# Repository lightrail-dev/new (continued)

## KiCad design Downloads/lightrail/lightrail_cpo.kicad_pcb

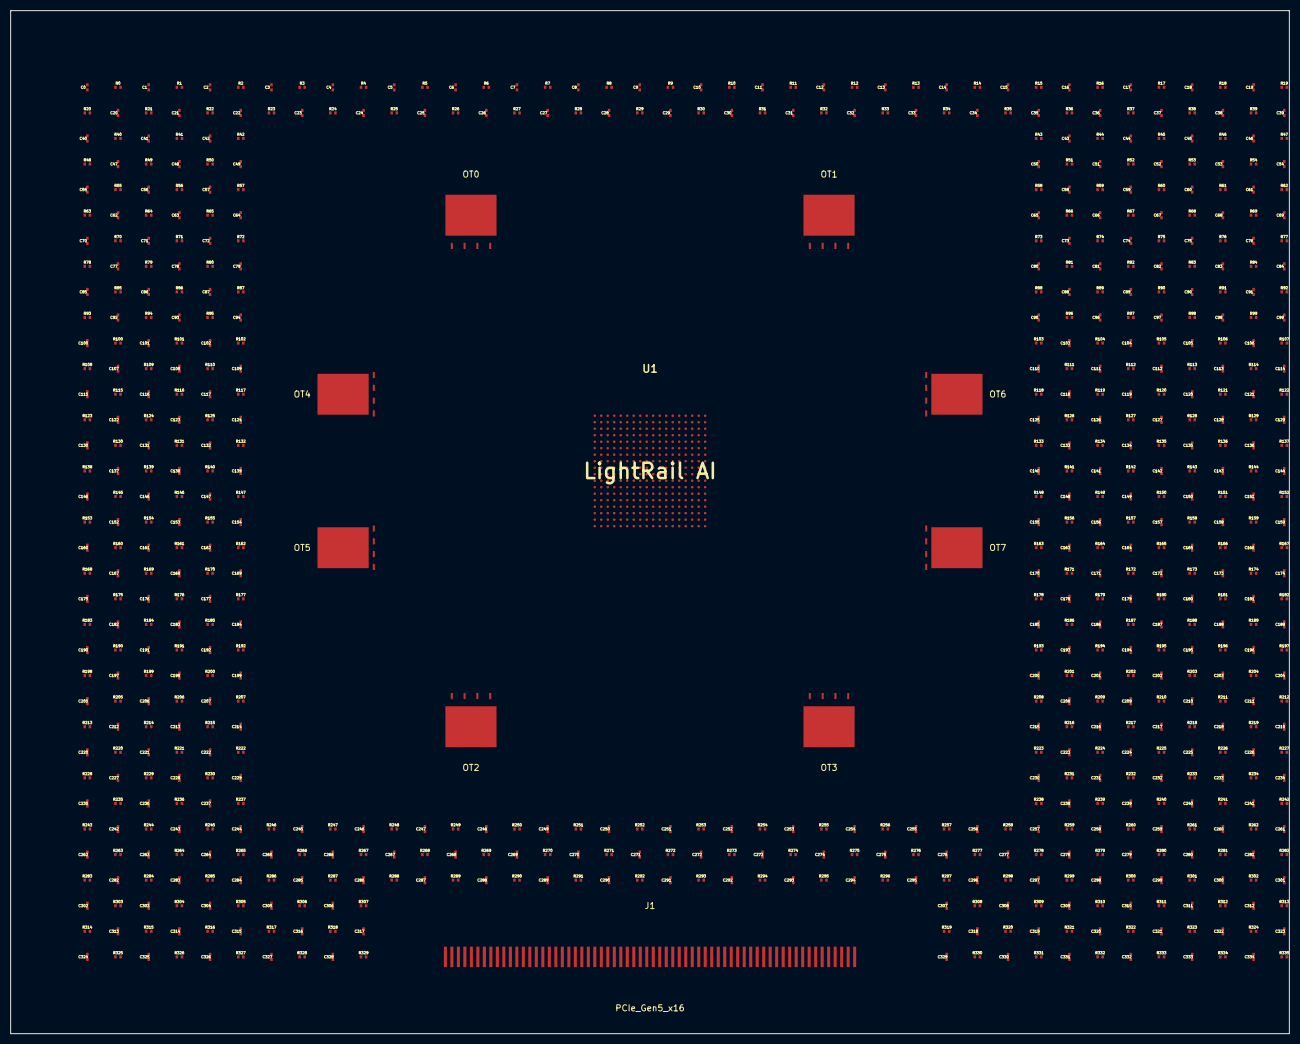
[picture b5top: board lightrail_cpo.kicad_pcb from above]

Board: 15 copper layers, 250.0 x 200.0 mm, 681 parts (0 on the bottom side), 77 nets, no tracks yet.

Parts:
C0, C1, C2, C3, C4, C5, C6, C7, C8, C9, C10, C11, C12, C13, C14, C15, C16, C17, C18, C19, C20, C21, C22, C23, C24, C25, C26, C27, C28, C29, C30, C31, C32, C33, C34, C35, C36, C37, C38, C39, C40, C41, C42, C43, C44, C45, C46, C47, C48, C49, C50, C51, C52, C53, C54, C55, C56, C57, C58, C59, C60, C61, C62, C63, C64, C65, C66, C67, C68, C69, C70, C71, C72, C73, C74, C75, C76, C77, C78, C79, C80, C81, C82, C83, C84, C85, C86, C87, C88, C89, C90, C91, C92, C93, C94, C95, C96, C97, C98, C99, C100, C101, C102, C103, C104, C105, C106, C107, C108, C109, C110, C111, C112, C113, C114, C115, C116, C117, C118, C119, C120, C121, C122, C123, C124, C125, C126, C127, C128, C129, C130, C131, C132, C133, C134, C135, C136, C137, C138, C139, C140, C141, C142, C143, C144, C145, C146, C147, C148, C149, C150, C151, C152, C153, C154, C155, C156, C157, C158, C159, C160, C161, C162, C163, C164, C165, C166, C167, C168, C169, C170, C171, C172, C173, C174, C175, C176, C177, C178, C179, C180, C181, C182, C183, C184, C185, C186, C187, C188, C189, C190, C191, C192, C193, C194, C195, C196, C197, C198, C199, C200, C201, C202, C203, C204, C205, C206, C207, C208, C209, C210, C211, C212, C213, C214, C215, C216, C217, C218, C219, C220, C221, C222, C223, C224, C225, C226, C227, C228, C229, C230, C231, C232, C233, C234, C235, C236, C237, C238, C239, C240, C241, C242, C243, C244, C245, C246, C247, C248, C249, C250, C251, C252, C253, C254, C255, C256, C257, C258, C259, C260, C261, C262, C263, C264, C265, C266, C267, C268, C269, C270, C271, C272, C273, C274, C275, C276, C277, C278, C279, C280, C281, C282, C283, C284, C285, C286, C287, C288, C289, C290, C291, C292, C293, C294, C295, C296, C297, C298, C299, C300, C301, C302, C303, C304, C305, C306, C307, C308, C309, C310, C311, C312, C313, C314, C315, C316, C317, C318, C319, C320, C321, C322, C323, C324, C325, C326, C327, C328, C329, C330, C331, C332, C333, C334: C; C_0402_1005Metric
J1: PCIe_Gen5_x16; PCIe_x16
OT0, OT1, OT2, OT3, OT4, OT5, OT6, OT7: O_TILE_TFLN
R0, R1, R2, R3, R4, R5, R6, R7, R8, R9, R10, R11, R12, R13, R14, R15, R16, R17, R18, R19, R20, R21, R22, R23, R24, R25, R26, R27, R28, R29, R30, R31, R32, R33, R34, R35, R36, R37, R38, R39, R40, R41, R42, R43, R44, R45, R46, R47, R48, R49, R50, R51, R52, R53, R54, R55, R56, R57, R58, R59, R60, R61, R62, R63, R64, R65, R66, R67, R68, R69, R70, R71, R72, R73, R74, R75, R76, R77, R78, R79, R80, R81, R82, R83, R84, R85, R86, R87, R88, R89, R90, R91, R92, R93, R94, R95, R96, R97, R98, R99, R100, R101, R102, R103, R104, R105, R106, R107, R108, R109, R110, R111, R112, R113, R114, R115, R116, R117, R118, R119, R120, R121, R122, R123, R124, R125, R126, R127, R128, R129, R130, R131, R132, R133, R134, R135, R136, R137, R138, R139, R140, R141, R142, R143, R144, R145, R146, R147, R148, R149, R150, R151, R152, R153, R154, R155, R156, R157, R158, R159, R160, R161, R162, R163, R164, R165, R166, R167, R168, R169, R170, R171, R172, R173, R174, R175, R176, R177, R178, R179, R180, R181, R182, R183, R184, R185, R186, R187, R188, R189, R190, R191, R192, R193, R194, R195, R196, R197, R198, R199, R200, R201, R202, R203, R204, R205, R206, R207, R208, R209, R210, R211, R212, R213, R214, R215, R216, R217, R218, R219, R220, R221, R222, R223, R224, R225, R226, R227, R228, R229, R230, R231, R232, R233, R234, R235, R236, R237, R238, R239, R240, R241, R242, R243, R244, R245, R246, R247, R248, R249, R250, R251, R252, R253, R254, R255, R256, R257, R258, R259, R260, R261, R262, R263, R264, R265, R266, R267, R268, R269, R270, R271, R272, R273, R274, R275, R276, R277, R278, R279, R280, R281, R282, R283, R284, R285, R286, R287, R288, R289, R290, R291, R292, R293, R294, R295, R296, R297, R298, R299, R300, R301, R302, R303, R304, R305, R306, R307, R308, R309, R310, R311, R312, R313, R314, R315, R316, R317, R318, R319, R320, R321, R322, R323, R324, R325, R326, R327, R328, R329, R330, R331, R332, R333, R334, R335: R; R_0402_1005Metric
U1: LightRail AI; BGA-324

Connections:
GND: C0.2, C1.2, C2.2, C3.2, C4.2, C5.2, C6.2, C7.2, C8.2, C9.2, C10.2, C11.2, C12.2, C13.2, C14.2, C15.2, C16.2, C17.2, C18.2, C19.2, C20.2, C21.2, C22.2, C23.2, C24.2, C25.2, C26.2, C27.2, C28.2, C29.2, C30.2, C31.2, C32.2, C33.2, C34.2, C35.2, C36.2, C37.2, C38.2, C39.2, C40.2, C41.2, C42.2, C43.2, C44.2, C45.2, C46.2, C47.2, C48.2, C49.2, C50.2, C51.2, C52.2, C53.2, C54.2, C55.2, C56.2, C57.2, C58.2, C59.2, C60.2, C61.2, C62.2, C63.2, C64.2, C65.2, C66.2, C67.2, C68.2, C69.2, C70.2, C71.2, C72.2, C73.2, C74.2, C75.2, C76.2, C77.2, C78.2, C79.2, C80.2, C81.2, C82.2, C83.2, C84.2, C85.2, C86.2, C87.2, C88.2, C89.2, C90.2, C91.2, C92.2, C93.2, C94.2, C95.2, C96.2, C97.2, C98.2, C99.2, C100.2, C101.2, C102.2, C103.2, C104.2, C105.2, C106.2, C107.2, C108.2, C109.2, C110.2, C111.2, C112.2, C113.2, C114.2, C115.2, C116.2, C117.2, C118.2, C119.2, C120.2, C121.2, C122.2, C123.2, C124.2, C125.2, C126.2, C127.2, C128.2, C129.2, C130.2, C131.2, C132.2, C133.2, C134.2, C135.2, C136.2, C137.2, C138.2, C139.2, C140.2, C141.2, C142.2, C143.2, C144.2, C145.2, C146.2, C147.2, C148.2, C149.2, C150.2, C151.2, C152.2, C153.2, C154.2, C155.2, C156.2, C157.2, C158.2, C159.2, C160.2, C161.2, C162.2, C163.2, C164.2, C165.2, C166.2, C167.2, C168.2, C169.2, C170.2, C171.2, C172.2, C173.2, C174.2, C175.2, C176.2, C177.2, C178.2, C179.2, C180.2, C181.2, C182.2, C183.2, C184.2, C185.2, C186.2, C187.2, C188.2, C189.2, C190.2, C191.2, C192.2, C193.2, C194.2, C195.2, C196.2, C197.2, C198.2, C199.2, C200.2, C201.2, C202.2, C203.2, C204.2, C205.2, C206.2, C207.2, C208.2, C209.2, C210.2, C211.2, C212.2, C213.2, C214.2, C215.2, C216.2, C217.2, C218.2, C219.2, C220.2, C221.2, C222.2, C223.2, C224.2, C225.2, C226.2, C227.2, C228.2, C229.2, C230.2, C231.2, C232.2, C233.2, C234.2, C235.2, C236.2, C237.2, C238.2, C239.2, C240.2, C241.2, C242.2, C243.2, C244.2, C245.2, C246.2, C247.2, C248.2, C249.2, C250.2, C251.2, C252.2, C253.2, C254.2, C255.2, C256.2, C257.2, C258.2, C259.2, C260.2, C261.2, C262.2, C263.2, C264.2, C265.2, C266.2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
NCE_PCIE_L0: J1.1, R32.1, R94.1, R116.1, R149.1, R159.1, R165.1, R284.1, R327.1, U1.1
NCE_PCIE_L1: J1.2, R150.1, R328.1, U1.2
NCE_PCIE_L2: J1.3, R53.1, R83.1, R244.1, R321.1, R331.1, U1.3
NCE_PCIE_L3: J1.4, R108.1, R223.1, R280.1, R318.1, U1.4
NCE_PCIE_L4: J1.5, R16.1, R48.1, R92.1, R189.1, R206.1, R220.1, R251.1, U1.5
NCE_PCIE_L5: J1.6, R28.1, R42.1, R81.1, R194.1, R241.1, R273.1, R277.1, U1.6
NCE_PCIE_L6: J1.7, R78.1, R120.1, R221.1, R297.1, U1.7
NCE_PCIE_L7: J1.8, R69.1, R98.1, U1.8
NCE_PCIE_L8: J1.9, R31.1, R109.1, R147.1, R156.1, R205.1, R239.1, R258.1, U1.9
NCE_PCIE_L9: J1.10, R65.1, R124.1, R197.1, R230.1, R247.1, R255.1, R314.1, U1.10
NCE_PCIE_L10: J1.11, R142.1, R183.1, R228.1, R299.1, U1.11
NCE_PCIE_L11: J1.12, R52.1, R85.1, R96.1, R101.1, R117.1, R174.1, R237.1, U1.12
NCE_PCIE_L12: J1.13, R55.1, R84.1, R113.1, R132.1, R195.1, R213.1, R270.1, U1.13
NCE_PCIE_L13: J1.14, R23.1, R264.1, R271.1, R326.1, U1.14
NCE_PCIE_L14: J1.15, R11.1, R45.1, R166.1, U1.15
NCE_PCIE_L15: J1.16, R119.1, R163.1, R164.1, R182.1, R216.1, R289.1, U1.16
NCE_PCIE_L16: J1.17, R198.1, R298.1, R307.1, U1.17
NCE_PCIE_L17: J1.18, R24.1, R47.1, R125.1, R131.1, R246.1, R288.1, R311.1, U1.18
NCE_PCIE_L18: J1.19, R38.1, R115.1, R153.1, R199.1, R224.1, R235.1, U1.19
NCE_PCIE_L19: J1.20, R29.1, R87.1, R152.1, R168.1, R175.1, R181.1, U1.20
NCE_PCIE_L20: J1.21, R12.1, R41.1, R208.1, R262.1, R306.1, U1.21
NCE_PCIE_L21: J1.22, R79.1, R104.1, R137.1, R173.1, R211.1, R249.1, R286.1, U1.22
NCE_PCIE_L22: J1.23, R103.1, R138.1, R186.1, R207.1, R212.1, R253.1, R278.1, U1.23
NCE_PCIE_L23: J1.24, R2.1, R54.1, R95.1, R154.1, R179.1, R188.1, R272.1, R290.1, U1.24
NCE_PCIE_L24: J1.25, R171.1, U1.25
NCE_PCIE_L25: J1.26, R35.1, R56.1, R106.1, R193.1, R243.1, R317.1, R330.1, U1.26
NCE_PCIE_L26: J1.27, R61.1, R90.1, R148.1, R232.1, R238.1, R242.1, U1.27
NCE_PCIE_L27: J1.28, R15.1, R62.1, R89.1, R203.1, R281.1, R287.1, R324.1, U1.28
NCE_PCIE_L28: J1.29, R70.1, R74.1, R86.1, R126.1, R222.1, R254.1, R296.1, U1.29
NCE_PCIE_L29: J1.30, R139.1, R279.1, R294.1, R325.1, U1.30
NCE_PCIE_L30: J1.31, R14.1, R17.1, R93.1, R140.1, R191.1, R196.1, R257.1, U1.31
NCE_PCIE_L31: J1.32, R34.1, R129.1, R141.1, R167.1, R214.1, U1.32
NCE_PCIE_L32: J1.33, R63.1, R172.1, R233.1, U1.33
NCE_PCIE_L33: J1.34, R1.1, R43.1, R44.1, R49.1, R112.1, U1.34
NCE_PCIE_L34: J1.35, R110.1, R170.1, R252.1, U1.35
NCE_PCIE_L35: J1.36, R6.1, R107.1, R133.1, U1.36
NCE_PCIE_L36: J1.37, R46.1, R136.1, R231.1, R315.1, R335.1, U1.37
NCE_PCIE_L37: J1.38, R121.1, R135.1, R145.1, R176.1, R204.1, R210.1, R329.1, U1.38
NCE_PCIE_L38: J1.39, R68.1, R82.1, R97.1, R250.1, U1.39
NCE_PCIE_L39: J1.40, R57.1, R77.1, R122.1, R295.1, U1.40
NCE_PCIE_L40: J1.41, R245.1, R268.1, R322.1, U1.41
NCE_PCIE_L41: J1.42, R8.1, R36.1, R37.1, U1.42
NCE_PCIE_L42: J1.43, R218.1, R227.1, R283.1, R309.1, U1.43
NCE_PCIE_L43: J1.44, R234.1, R261.1, R285.1, R300.1, R301.1, R332.1, U1.44
NCE_PCIE_L44: J1.45, R114.1, R127.1, R209.1, R225.1, R267.1, U1.45
NCE_PCIE_L45: J1.46, R20.1, R157.1, R202.1, R308.1, U1.46
NCE_PCIE_L46: J1.47, R13.1, R27.1, R143.1, R178.1, R303.1, U1.47
NCE_PCIE_L47: J1.48, R22.1, R59.1, R88.1, R130.1, R160.1, R282.1, U1.48
NCE_PCIE_L48: J1.49, R64.1, R72.1, R105.1, R123.1, R269.1, R334.1, U1.49
NCE_PCIE_L49: J1.50, R80.1, R260.1, R316.1, U1.50
NCE_PCIE_L50: J1.51, R73.1, R91.1, R146.1, R155.1, R180.1, U1.51
NCE_PCIE_L51: J1.52, R4.1, R10.1, R58.1, R144.1, R162.1, R226.1, U1.52
NCE_PCIE_L52: J1.53, R51.1, R60.1, R118.1, R274.1, R302.1, U1.53
NCE_PCIE_L53: J1.54, R3.1, R134.1, R192.1, R200.1, R266.1, R320.1, U1.54
NCE_PCIE_L54: J1.55, R67.1, R158.1, R248.1, U1.55
NCE_PCIE_L55: J1.56, R75.1, R76.1, R99.1, R128.1, R263.1, R313.1, R319.1, U1.56
NCE_PCIE_L56: J1.57, R0.1, R26.1, R177.1, R187.1, R215.1, R240.1, R259.1, U1.57
NCE_PCIE_L57: J1.58, R7.1, R21.1, R184.1, R236.1, U1.58
NCE_PCIE_L58: J1.59, R9.1, R40.1, R102.1, R185.1, R201.1, R275.1, R291.1, R310.1, R323.1, U1.59
NCE_PCIE_L59: J1.60, R18.1, R33.1, R71.1, R100.1, R190.1, R217.1, R256.1, U1.60
NCE_PCIE_L60: J1.61, R151.1, R161.1, R219.1, R276.1, R304.1, U1.61
NCE_PCIE_L61: J1.62, R265.1, R305.1, R312.1, U1.62
NCE_PCIE_L62: J1.63, R5.1, R19.1, R25.1, R30.1, R39.1, R66.1, R229.1, U1.63
NCE_PCIE_L63: J1.64, R50.1, R111.1, R169.1, R292.1, R293.1, R333.1, U1.64
O_TILE_0_RF_0: OT0.1, U1.65, U1.73, U1.81, U1.89, U1.97, U1.105, U1.113, U1.121
O_TILE_1_RF_1: OT1.2, U1.66, U1.74, U1.82, U1.90, U1.98, U1.106, U1.114, U1.122
O_TILE_2_RF_2: OT2.3, U1.67, U1.75, U1.83, U1.91, U1.99, U1.107, U1.115, U1.123
O_TILE_3_RF_3: OT3.4, U1.68, U1.76, U1.84, U1.92, U1.100, U1.108, U1.116, U1.124
O_TILE_4_RF_0: OT4.1, U1.69, U1.77, U1.85, U1.93, U1.101, U1.109, U1.117, U1.125
O_TILE_5_RF_1: OT5.2, U1.70, U1.78, U1.86, U1.94, U1.102, U1.110, U1.118, U1.126
O_TILE_6_RF_2: OT6.3, U1.71, U1.79, U1.87, U1.95, U1.103, U1.111, U1.119, U1.127
O_TILE_7_RF_3: OT7.4, U1.72, U1.80, U1.88, U1.96, U1.104, U1.112, U1.120, U1.128
VCC_1V0: U1.134, U1.135, U1.136, U1.137, U1.138, U1.152, U1.153, U1.154, U1.155, U1.156, U1.170, U1.171, U1.172, U1.173, U1.174, U1.188, U1.189, U1.190, U1.191, U1.192, U1.206, U1.207, U1.208, U1.209, U1.210
VCC_1V8: C0.1, C2.1, C3.1, C5.1, C9.1, C17.1, C18.1, C20.1, C24.1, C25.1, C26.1, C28.1, C31.1, C35.1, C37.1, C39.1, C40.1, C43.1, C48.1, C55.1, C60.1, C63.1, C65.1, C70.1, C78.1, C79.1, C87.1, C89.1, C90.1, C91.1, C92.1, C95.1, C107.1, C113.1, C116.1, C118.1, C119.1, C120.1, C122.1, C125.1, C130.1, C133.1, C136.1, C138.1, C139.1, C143.1, C145.1, C146.1, C150.1, C151.1, C155.1, C157.1, C160.1, C166.1, C167.1, C171.1, C174.1, C176.1, C177.1, C178.1, C179.1, C184.1, C185.1, C186.1, C187.1, C189.1, C193.1, C194.1, C195.1, C196.1, C198.1, C200.1, C201.1, C204.1, C207.1, C209.1, C210.1, C211.1, C213.1, C215.1, C217.1, C219.1, C220.1, C227.1, C229.1, C231.1, C233.1, C234.1, C239.1, C241.1, C243.1, C245.1, C253.1, C262.1, C265.1, C267.1, C270.1, C272.1, C274.1, C277.1, C286.1, C288.1, C297.1, C305.1, C306.1, C308.1, C310.1, C311.1, C318.1, C319.1, C322.1, C324.1, C330.1, C332.1
VCC_3V3: C1.1, C10.1, C12.1, C16.1, C19.1, C22.1, C27.1, C30.1, C33.1, C36.1, C38.1, C41.1, C42.1, C44.1, C45.1, C47.1, C51.1, C52.1, C54.1, C56.1, C58.1, C59.1, C62.1, C66.1, C67.1, C69.1, C71.1, C76.1, C80.1, C81.1, C83.1, C86.1, C88.1, C94.1, C96.1, C97.1, C98.1, C99.1, C100.1, C106.1, C111.1, C115.1, C117.1, C123.1, C127.1, C128.1, C132.1, C137.1, C140.1, C144.1, C147.1, C148.1, C158.1, C159.1, C161.1, C162.1, C164.1, C169.1, C172.1, C183.1, C190.1, C202.1, C208.1, C216.1, C218.1, C223.1, C225.1, C228.1, C230.1, C232.1, C235.1, C236.1, C237.1, C238.1, C240.1, C242.1, C244.1, C246.1, C247.1, C249.1, C250.1, C252.1, C257.1, C259.1, C264.1, C268.1, C269.1, C271.1, C275.1, C280.1, C281.1, C282.1, C285.1, C289.1, C293.1, C294.1, C300.1, C302.1, C303.1, C304.1, C307.1, C312.1, C315.1, C316.1, C317.1, C321.1, C327.1, C329.1, C331.1
VCC_12V: C4.1, C6.1, C7.1, C8.1, C11.1, C13.1, C14.1, C15.1, C21.1, C23.1, C29.1, C32.1, C34.1, C46.1, C49.1, C50.1, C53.1, C57.1, C61.1, C64.1, C68.1, C72.1, C73.1, C74.1, C75.1, C77.1, C82.1, C84.1, C85.1, C93.1, C101.1, C102.1, C103.1, C104.1, C105.1, C108.1, C109.1, C110.1, C112.1, C114.1, C121.1, C124.1, C126.1, C129.1, C131.1, C134.1, C135.1, C141.1, C142.1, C149.1, C152.1, C153.1, C154.1, C156.1, C163.1, C165.1, C168.1, C170.1, C173.1, C175.1, C180.1, C181.1, C182.1, C188.1, C191.1, C192.1, C197.1, C199.1, C203.1, C205.1, C206.1, C212.1, C214.1, C221.1, C222.1, C224.1, C226.1, C248.1, C251.1, C254.1, C255.1, C256.1, C258.1, C260.1, C261.1, C263.1, C266.1, C273.1, C276.1, C278.1, C279.1, C283.1, C284.1, C287.1, C290.1, C291.1, C292.1, C295.1, C296.1, C298.1, C299.1, C301.1, C309.1, C313.1, C314.1, C320.1, C323.1, C325.1, C326.1, C328.1, C333.1, C334.1

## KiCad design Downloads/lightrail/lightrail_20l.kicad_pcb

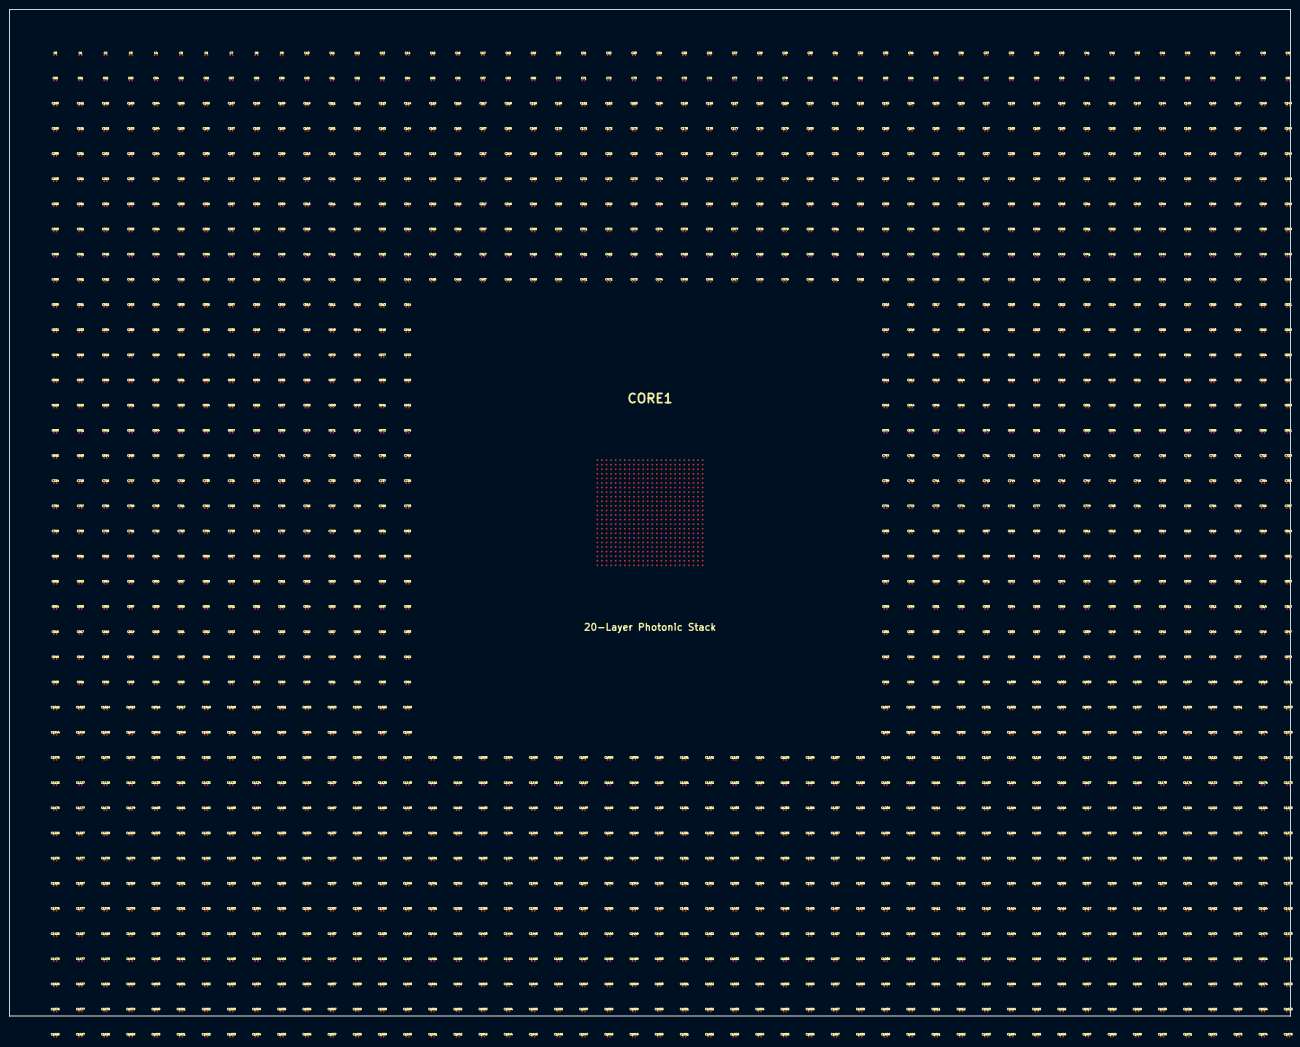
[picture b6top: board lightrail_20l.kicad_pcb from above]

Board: 20 copper layers, 280.0 x 220.0 mm, 1677 parts (0 on the bottom side), 235 nets, no tracks yet.

Parts:
C0, C1, C2, C3, C4, C5, C6, C7, C8, C9, C10, C11, C12, C13, C14, C15, C16, C17, C18, C19, C20, C21, C22, C23, C24, C25, C26, C27, C28, C29, C30, C31, C32, C33, C34, C35, C36, C37, C38, C39, C40, C41, C42, C43, C44, C45, C46, C47, C48, C49, C50, C51, C52, C53, C54, C55, C56, C57, C58, C59, C60, C61, C62, C63, C64, C65, C66, C67, C68, C69, C70, C71, C72, C73, C74, C75, C76, C77, C78, C79, C80, C81, C82, C83, C84, C85, C86, C87, C88, C89, C90, C91, C92, C93, C94, C95, C96, C97, C98, C99, C100, C101, C102, C103, C104, C105, C106, C107, C108, C109, C110, C111, C112, C113, C114, C115, C116, C117, C118, C119, C120, C121, C122, C123, C124, C125, C126, C127, C128, C129, C130, C131, C132, C133, C134, C135, C136, C137, C138, C139, C140, C141, C142, C143, C144, C145, C146, C147, C148, C149, C150, C151, C152, C153, C154, C155, C156, C157, C158, C159, C160, C161, C162, C163, C164, C165, C166, C167, C168, C169, C170, C171, C172, C173, C174, C175, C176, C177, C178, C179, C180, C181, C182, C183, C184, C185, C186, C187, C188, C189, C190, C191, C192, C193, C194, C195, C196, C197, C198, C199, C200, C201, C202, C203, C204, C205, C206, C207, C208, C209, C210, C211, C212, C213, C214, C215, C216, C217, C218, C219, C220, C221, C222, C223, C224, C225, C226, C227, C228, C229, C230, C231, C232, C233, C234, C235, C236, C237, C238, C239, C240, C241, C242, C243, C244, C245, C246, C247, C248, C249, C250, C251, C252, C253, C254, C255, C256, C257, C258, C259, C260, C261, C262, C263, C264, C265, C266, C267, C268, C269, C270, C271, C272, C273, C274, C275, C276, C277, C278, C279, C280, C281, C282, C283, C284, C285, C286, C287, C288, C289, C290, C291, C292, C293, C294, C295, C296, C297, C298, C299, C300, C301, C302, C303, C304, C305, C306, C307, C308, C309, C310, C311, C312, C313, C314, C315, C316, C317, C318, C319, C320, C321, C322, C323, C324, C325, C326, C327, C328, C329, C330, C331, C332, C333, C334, C335, C336, C337, C338, C339, C340, C341, C342, C343, C344, C345, C346, C347, C348, C349, C350, C351, C352, C353, C354, C355, C356, C357, C358, C359, C360, C361, C362, C363, C364, C365, C366, C367, C368, C369, C370, C371, C372, C373, C374, C375, C376, C377, C378, C379, C380, C381, C382, C383, C384, C385, C386, C387, C388, C389, C390, C391, C392, C393, C394, C395, C396, C397, C398, C399, C400, C401, C402, C403, C404, C405, C406, C407, C408, C409, C410, C411, C412, C413, C414, C415, C416, C417, C418, C419, C420, C421, C422, C423, C424, C425, C426, C427, C428, C429, C430, C431, C432, C433, C434, C435, C436, C437, C438, C439, C440, C441, C442, C443, C444, C445, C446, C447, C448, C449, C450, C451, C452, C453, C454, C455, C456, C457, C458, C459, C460, C461, C462, C463, C464, C465, C466, C467, C468, C469, C470, C471, C472, C473, C474, C475, C476, C477, C478, C479, C480, C481, C482, C483, C484, C485, C486, C487, C488, C489, C490, C491, C492, C493, C494, C495, C496, C497, C498, C499, C500, C501, C502, C503, C504, C505, C506, C507, C508, C509, C510, C511, C512, C513, C514, C515, C516, C517, C518, C519, C520, C521, C522, C523, C524, C525, C526, C527, C528, C529, C530, C531, C532, C533, C534, C535, C536, C537, C538, C539, C540, C541, C542, C543, C544, C545, C546, C547, C548, C549, C550, C551, C552, C553, C554, C555, C556, C557, C558, C559, C560, C561, C562, C563, C564, C565, C566, C567, C568, C569, C570, C571, C572, C573, C574, C575, C576, C577, C578, C579, C580, C581, C582, C583, C584, C585, C586, C587, C588, C589, C590, C591, C592, C593, C594, C595, C596, C597, C598, C599, C600, C601, C602, C603, C604, C605, C606, C607, C608, C609, C610, C611, C612, C613, C614, C615, C616, C617, C618, C619, C620, C621, C622, C623, C624, C625, C626, C627, C628, C629, C630, C631, C632, C633, C634, C635, C636, C637, C638, C639, C640, C641, C642, C643, C644, C645, C646, C647, C648, C649, C650, C651, C652, C653, C654, C655, C656, C657, C658, C659, C660, C661, C662, C663, C664, C665, C666, C667, C668, C669, C670, C671, C672, C673, C674, C675, C676, C677, C678, C679, C680, C681, C682, C683, C684, C685, C686, C687, C688, C689, C690, C691, C692, C693, C694, C695, C696, C697, C698, C699, C700, C701, C702, C703, C704, C705, C706, C707, C708, C709, C710, C711, C712, C713, C714, C715, C716, C717, C718, C719, C720, C721, C722, C723, C724, C725, C726, C727, C728, C729, C730, C731, C732, C733, C734, C735, C736, C737, C738, C739, C740, C741, C742, C743, C744, C745, C746, C747, C748, C749, C750, C751, C752, C753, C754, C755, C756, C757, C758, C759, C760, C761, C762, C763, C764, C765, C766, C767, C768, C769, C770, C771, C772, C773, C774, C775, C776, C777, C778, C779, C780, C781, C782, C783, C784, C785, C786, C787, C788, C789, C790, C791, C792, C793, C794, C795, C796, C797, C798, C799, C800, C801, C802, C803, C804, C805, C806, C807, C808, C809, C810, C811, C812, C813, C814, C815, C816, C817, C818, C819, C820, C821, C822, C823, C824, C825, C826, C827, C828, C829, C830, C831, C832, C833, C834, C835, C836, C837, C838, C839, C840, C841, C842, C843, C844, C845, C846, C847, C848, C849, C850, C851, C852, C853, C854, C855, C856, C857, C858, C859, C860, C861, C862, C863, C864, C865, C866, C867, C868, C869, C870, C871, C872, C873, C874, C875, C876, C877, C878, C879, C880, C881, C882, C883, C884, C885, C886, C887, C888, C889, C890, C891, C892, C893, C894, C895, C896, C897, C898, C899, C900, C901, C902, C903, C904, C905, C906, C907, C908, C909, C910, C911, C912, C913, C914, C915, C916, C917, C918, C919, C920, C921, C922, C923, C924, C925, C926, C927, C928, C929, C930, C931, C932, C933, C934, C935, C936, C937, C938, C939, C940, C941, C942, C943, C944, C945, C946, C947, C948, C949, C950, C951, C952, C953, C954, C955, C956, C957, C958, C959, C960, C961, C962, C963, C964, C965, C966, C967, C968, C969, C970, C971, C972, C973, C974, C975, C976, C977, C978, C979, C980, C981, C982, C983, C984, C985, C986, C987, C988, C989, C990, C991, C992, C993, C994, C995, C996, C997, C998, C999, C1000, C1001, C1002, C1003, C1004, C1005, C1006, C1007, C1008, C1009, C1010, C1011, C1012, C1013, C1014, C1015, C1016, C1017, C1018, C1019, C1020, C1021, C1022, C1023, C1024, C1025, C1026, C1027, C1028, C1029, C1030, C1031, C1032, C1033, C1034, C1035, C1036, C1037, C1038, C1039, C1040, C1041, C1042, C1043, C1044, C1045, C1046, C1047, C1048, C1049, C1050, C1051, C1052, C1053, C1054, C1055, C1056, C1057, C1058, C1059, C1060, C1061, C1062, C1063, C1064, C1065, C1066, C1067, C1068, C1069, C1070, C1071, C1072, C1073, C1074, C1075, C1076, C1077, C1078, C1079, C1080, C1081, C1082, C1083, C1084, C1085, C1086, C1087, C1088, C1089, C1090, C1091, C1092, C1093, C1094, C1095, C1096, C1097, C1098, C1099, C1100, C1101, C1102, C1103, C1104, C1105, C1106, C1107, C1108, C1109, C1110, C1111, C1112, C1113, C1114, C1115, C1116, C1117, C1118, C1119, C1120, C1121, C1122, C1123, C1124, C1125, C1126, C1127, C1128, C1129, C1130, C1131, C1132, C1133, C1134, C1135, C1136, C1137, C1138, C1139, C1140, C1141, C1142, C1143, C1144, C1145, C1146, C1147, C1148, C1149, C1150, C1151, C1152, C1153, C1154, C1155, C1156, C1157, C1158, C1159, C1160, C1161, C1162, C1163, C1164, C1165, C1166, C1167, C1168, C1169, C1170, C1171, C1172, C1173, C1174, C1175, C1176, C1177, C1178, C1179, C1180, C1181, C1182, C1183, C1184, C1185, C1186, C1187, C1188, C1189, C1190, C1191, C1192, C1193, C1194, C1195, C1196, C1197, C1198, C1199, C1200, C1201, C1202, C1203, C1204, C1205, C1206, C1207, C1208, C1209, C1210, C1211, C1212, C1213, C1214, C1215, C1216, C1217, C1218, C1219, C1220, C1221, C1222, C1223, C1224, C1225, C1226, C1227, C1228, C1229, C1230, C1231, C1232, C1233, C1234, C1235, C1236, C1237, C1238, C1239, C1240, C1241, C1242, C1243, C1244, C1245, C1246, C1247, C1248, C1249, C1250, C1251, C1252, C1253, C1254, C1255, C1256, C1257, C1258, C1259, C1260, C1261, C1262, C1263, C1264, C1265, C1266, C1267, C1268, C1269, C1270, C1271, C1272, C1273, C1274, C1275, C1276, C1277, C1278, C1279, C1280, C1281, C1282, C1283, C1284, C1285, C1286, C1287, C1288, C1289, C1290, C1291, C1292, C1293, C1294, C1295, C1296, C1297, C1298, C1299, C1300, C1301, C1302, C1303, C1304, C1305, C1306, C1307, C1308, C1309, C1310, C1311, C1312, C1313, C1314, C1315, C1316, C1317, C1318, C1319, C1320, C1321, C1322, C1323, C1324, C1325, C1326, C1327, C1328, C1329, C1330, C1331, C1332, C1333, C1334, C1335, C1336, C1337, C1338, C1339, C1340, C1341, C1342, C1343, C1344, C1345, C1346, C1347, C1348, C1349, C1350, C1351, C1352, C1353, C1354, C1355, C1356, C1357, C1358, C1359, C1360, C1361, C1362, C1363, C1364, C1365, C1366, C1367, C1368, C1369, C1370, C1371, C1372, C1373, C1374, C1375, C1376, C1377, C1378, C1379, C1380, C1381, C1382, C1383, C1384, C1385, C1386, C1387, C1388, C1389, C1390, C1391, C1392, C1393, C1394, C1395, C1396, C1397, C1398, C1399, C1400, C1401, C1402, C1403, C1404, C1405, C1406, C1407, C1408, C1409, C1410, C1411, C1412, C1413, C1414, C1415, C1416, C1417, C1418, C1419, C1420, C1421, C1422, C1423, C1424, C1425, C1426, C1427, C1428, C1429, C1430, C1431, C1432, C1433, C1434, C1435, C1436, C1437, C1438, C1439, C1440, C1441, C1442, C1443, C1444, C1445, C1446, C1447, C1448, C1449, C1450, C1451, C1452, C1453, C1454, C1455, C1456, C1457, C1458, C1459, C1460, C1461, C1462, C1463, C1464, C1465, C1466, C1467, C1468, C1469, C1470, C1471, C1472, C1473, C1474, C1475, C1476, C1477, C1478, C1479, C1480, C1481, C1482, C1483, C1484, C1485, C1486, C1487, C1488, C1489, C1490, C1491, C1492, C1493, C1494, C1495, C1496, C1497, C1498, C1499, C1500, C1501, C1502, C1503, C1504, C1505, C1506, C1507, C1508, C1509, C1510, C1511, C1512, C1513, C1514, C1515, C1516, C1517, C1518, C1519, C1520, C1521, C1522, C1523, C1524, C1525, C1526, C1527, C1528, C1529, C1530, C1531, C1532, C1533, C1534, C1535, C1536, C1537, C1538, C1539, C1540, C1541, C1542, C1543, C1544, C1545, C1546, C1547, C1548, C1549, C1550, C1551, C1552, C1553, C1554, C1555, C1556, C1557, C1558, C1559, C1560, C1561, C1562, C1563, C1564, C1565, C1566, C1567, C1568, C1569, C1570, C1571, C1572, C1573, C1574, C1575, C1576, C1577, C1578, C1579, C1580, C1581, C1582, C1583, C1584, C1585, C1586, C1587, C1588, C1589, C1590, C1591, C1592, C1593, C1594, C1595, C1596, C1597, C1598, C1599, C1600, C1601, C1602, C1603, C1604, C1605, C1606, C1607, C1608, C1609, C1610, C1611, C1612, C1613, C1614, C1615, C1616, C1617, C1618, C1619, C1620, C1621, C1622, C1623, C1624, C1625, C1626, C1627, C1628, C1629, C1630, C1631, C1632, C1633, C1634, C1635, C1636, C1637, C1638, C1639, C1640, C1641, C1642, C1643, C1644, C1645, C1646, C1647, C1648, C1649, C1650, C1651, C1652, C1653, C1654, C1655, C1656, C1657, C1658, C1659, C1660, C1661, C1662, C1663, C1664, C1665, C1666, C1667, C1668, C1669, C1670, C1671, C1672, C1673, C1674, C1675: C_0201_0603Metric
CORE1: 20-Layer Photonic Stack; IntelligenceStack_20L

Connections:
GND: C0.2, C1.2, C2.2, C3.2, C4.2, C5.1, C5.2, C6.2, C7.2, C8.1, C8.2, C9.2, C10.2, C11.2, C12.2, C13.2, C14.2, C15.1, C15.2, C16.1, C16.2, C17.2, C18.2, C19.2, C20.2, C21.2, C22.1, C22.2, C23.1, C23.2, C24.2, C25.2, C26.2, C27.2, C28.1, C28.2, C29.2, C30.1, C30.2, C31.2, C32.1, C32.2, C33.1, C33.2, C34.2, C35.2, C36.2, C37.1, C37.2, C38.1, C38.2, C39.1, C39.2, C40.2, C41.2, C42.2, C43.2, C44.2, C45.2, C46.2, C47.2, C48.2, C49.2, C50.2, C51.2, C52.1, C52.2, C53.2, C54.1, C54.2, C55.1, C55.2, C56.1, C56.2, C57.2, C58.1, C58.2, C59.2, C60.2, C61.1, C61.2, C62.1, C62.2, C63.2, C64.2, C65.1, C65.2, C66.2, C67.1, C67.2, C68.1, C68.2, C69.2, C70.1, C70.2, C71.2, C72.1, C72.2, C73.2, C74.2, C75.2, C76.2, C77.2, C78.2, C79.2, C80.2, C81.2, C82.1, C82.2, C83.2, C84.2, C85.2, C86.2, C87.2, C88.1, C88.2, C89.2, C90.2, C91.1, C91.2, C92.1, C92.2, C93.2, C94.1, C94.2, C95.2, C96.1, C96.2, C97.2, C98.1, C98.2, C99.2, C100.1, C100.2, C101.2, C102.2, C103.1, C103.2, C104.2, C105.1, C105.2, C106.2, C107.2, C108.2, C109.2, C110.2, C111.1, C111.2, C112.2, C113.2, C114.2, C115.1, C115.2, C116.2, C117.1, C117.2, C118.2, C119.2, C120.2, C121.1, C121.2, C122.2, C123.2, C124.2, C125.1, C125.2, C126.2, C127.2, C128.2, C129.2, C130.2, C131.2, C132.1, C132.2, C133.1, C133.2, C134.1, C134.2, C135.2, C136.2, C137.1, C137.2, C138.2, C139.1, C139.2, C140.1, C140.2, C141.1, C141.2, C142.2, C143.2, C144.2, C145.2, C146.2, C147.1, C147.2, C148.2, C149.2, C150.2, C151.2, C152.1, C152.2, C153.2, C154.1, C154.2, C155.2, C156.2, C157.2, C158.1, C158.2, C159.2, C160.2, C161.1, C161.2, C162.1, C162.2, C163.2, C164.2, C165.2, C166.2, C167.1, C167.2, C168.2, C169.2, C170.2, C171.2, C172.1, C172.2, C173.2, C174.1, C174.2, C175.2, C176.1, C176.2, C177.1, C177.2, C178.2, C179.2, C180.2, C181.2, C182.2, C183.2, C184.2, C185.1, C185.2, C186.2, C187.1, C187.2, C188.1, C188.2, C189.2, C190.2, C191.2, C192.2, C193.2, C194.2, C195.2, C196.1, C196.2, C197.1, C197.2, C198.2, C199.1, C199.2, C200.2, C201.1, C201.2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
V_ANALOG: C0.1, C2.1, C3.1, C6.1, C7.1, C10.1, C11.1, C17.1, C19.1, C20.1, C21.1, C31.1, C36.1, C41.1, C43.1, C44.1, C48.1, C57.1, C78.1, C79.1, C86.1, C95.1, C99.1, C102.1, C104.1, C107.1, C112.1, C118.1, C119.1, C120.1, C122.1, C127.1, C129.1, C135.1, C136.1, C138.1, C142.1, C151.1, C153.1, C155.1, C160.1, C163.1, C164.1, C168.1, C170.1, C171.1, C173.1, C175.1, C181.1, C182.1, C183.1, C186.1, C189.1, C194.1, C195.1, C198.1, C204.1, C210.1, C213.1, C217.1, C223.1, C224.1, C225.1, C226.1, C228.1, C229.1, C233.1, C237.1, C238.1, C239.1, C241.1, C243.1, C244.1, C245.1, C246.1, C248.1, C250.1, C251.1, C253.1, C258.1, C261.1, C262.1, C263.1, C264.1, C267.1, C274.1, C279.1, C281.1, C282.1, C283.1, C286.1, C287.1, C290.1, C292.1, C297.1, C302.1, C304.1, C308.1, C311.1, C313.1, C315.1, C316.1, C317.1, C320.1, C321.1, C323.1, C331.1, C334.1, C335.1, C337.1, C338.1, C345.1, C347.1, C348.1, C349.1, C357.1, C366.1, C373.1, C375.1, C377.1, C378.1, C382.1, C386.1, C387.1, C389.1, C392.1, C397.1, C401.1, C403.1, C404.1, C406.1, C408.1, C410.1, C423.1, C429.1, C431.1, C433.1, C434.1, C435.1, C440.1, C441.1, C443.1, C448.1, C452.1, C453.1, C454.1, C455.1, C456.1, C461.1, C463.1, C466.1, C468.1, C469.1, C470.1, C471.1, C480.1, C481.1, C483.1, C484.1, C485.1, C486.1, C489.1, C490.1, C491.1, C495.1, C497.1, C498.1, C499.1, C501.1, C503.1, C505.1, C506.1, C508.1, C510.1, C512.1, C514.1, C515.1, C517.1, C523.1, C524.1, C527.1, C534.1, C549.1, C551.1, C552.1, C555.1, C558.1, C561.1, C562.1, C563.1, C567.1, C570.1, C577.1, C578.1, C580.1, C585.1, C590.1, C592.1, C598.1, C601.1, C602.1, C603.1, C606.1, C609.1, C616.1, C619.1, C621.1, C622.1, C626.1, C629.1, C633.1, C639.1, C647.1, C648.1, C649.1, C650.1, C651.1, C654.1, C656.1, C659.1, C665.1, C667.1, C670.1, C671.1, C677.1, C681.1, C688.1, C690.1, C695.1, C698.1, C700.1, C701.1, C704.1, C709.1, C712.1, C713.1, C717.1, C719.1, C721.1, C726.1, C727.1, C728.1, C729.1, C731.1, C734.1, C735.1, C737.1, C740.1, C744.1, C745.1, C749.1, C750.1, C752.1, C755.1, C760.1, C762.1, C765.1, C766.1, C767.1, C769.1, C771.1, C779.1, C781.1, C784.1, C785.1, C786.1, C787.1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
V_LIGHT: C1.1, C4.1, C9.1, C12.1, C13.1, C14.1, C18.1, C24.1, C25.1, C26.1, C27.1, C29.1, C34.1, C35.1, C40.1, C42.1, C45.1, C46.1, C47.1, C49.1, C50.1, C51.1, C53.1, C59.1, C60.1, C63.1, C64.1, C66.1, C69.1, C71.1, C73.1, C74.1, C75.1, C76.1, C77.1, C80.1, C81.1, C83.1, C84.1, C85.1, C87.1, C89.1, C90.1, C93.1, C97.1, C101.1, C106.1, C108.1, C109.1, C110.1, C113.1, C114.1, C116.1, C123.1, C124.1, C126.1, C128.1, C130.1, C131.1, C143.1, C144.1, C145.1, C146.1, C148.1, C149.1, C150.1, C156.1, C157.1, C159.1, C165.1, C166.1, C169.1, C178.1, C179.1, C180.1, C184.1, C190.1, C191.1, C192.1, C193.1, C200.1, C208.1, C209.1, C212.1, C216.1, C219.1, C220.1, C222.1, C227.1, C235.1, C242.1, C247.1, C249.1, C257.1, C268.1, C270.1, C273.1, C275.1, C276.1, C277.1, C278.1, C280.1, C288.1, C296.1, C305.1, C306.1, C307.1, C309.1, C310.1, C314.1, C319.1, C322.1, C327.1, C330.1, C332.1, C336.1, C339.1, C342.1, C344.1, C350.1, C352.1, C353.1, C355.1, C360.1, C361.1, C362.1, C363.1, C368.1, C370.1, C371.1, C372.1, C374.1, C381.1, C384.1, C385.1, C390.1, C391.1, C394.1, C395.1, C398.1, C399.1, C400.1, C405.1, C407.1, C409.1, C413.1, C415.1, C416.1, C418.1, C419.1, C420.1, C421.1, C426.1, C427.1, C428.1, C430.1, C436.1, C438.1, C439.1, C446.1, C458.1, C459.1, C464.1, C472.1, C475.1, C476.1, C482.1, C488.1, C492.1, C493.1, C494.1, C507.1, C513.1, C516.1, C526.1, C528.1, C529.1, C530.1, C531.1, C535.1, C536.1, C538.1, C539.1, C545.1, C546.1, C547.1, C550.1, C553.1, C559.1, C565.1, C573.1, C575.1, C584.1, C586.1, C587.1, C588.1, C589.1, C591.1, C593.1, C595.1, C599.1, C607.1, C608.1, C610.1, C611.1, C615.1, C618.1, C628.1, C630.1, C632.1, C637.1, C638.1, C641.1, C642.1, C645.1, C646.1, C657.1, C658.1, C660.1, C661.1, C663.1, C664.1, C668.1, C676.1, C678.1, C680.1, C682.1, C686.1, C689.1, C693.1, C696.1, C697.1, C699.1, C702.1, C705.1, C706.1, C710.1, C714.1, C718.1, C720.1, C723.1, C733.1, C738.1, C741.1, C743.1, C746.1, C748.1, C751.1, C753.1, C754.1, C758.1, C763.1, C770.1, C772.1, C775.1, C777.1, C778.1, C780.1, C782.1, C788.1, C790.1, C797.1, C798.1, C799.1, C801.1, C804.1, C809.1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
WAVE_BUS_0: CORE1.1, CORE1.257, CORE1.513
WAVE_BUS_1: CORE1.2, CORE1.258, CORE1.514
WAVE_BUS_2: CORE1.3, CORE1.259, CORE1.515
WAVE_BUS_3: CORE1.4, CORE1.260, CORE1.516
WAVE_BUS_4: CORE1.5, CORE1.261, CORE1.517
WAVE_BUS_5: CORE1.6, CORE1.262, CORE1.518
WAVE_BUS_6: CORE1.7, CORE1.263, CORE1.519
WAVE_BUS_7: CORE1.8, CORE1.264, CORE1.520
WAVE_BUS_8: CORE1.9, CORE1.265, CORE1.521
WAVE_BUS_9: CORE1.10, CORE1.266, CORE1.522
WAVE_BUS_10: CORE1.11, CORE1.267, CORE1.523
WAVE_BUS_11: CORE1.12, CORE1.268, CORE1.524
WAVE_BUS_12: CORE1.13, CORE1.269, CORE1.525
WAVE_BUS_13: CORE1.14, CORE1.270, CORE1.526
WAVE_BUS_14: CORE1.15, CORE1.271, CORE1.527
WAVE_BUS_15: CORE1.16, CORE1.272, CORE1.528
WAVE_BUS_16: CORE1.17, CORE1.273, CORE1.529
WAVE_BUS_17: CORE1.18, CORE1.530
WAVE_BUS_18: CORE1.19, CORE1.531
WAVE_BUS_19: CORE1.20, CORE1.532
WAVE_BUS_20: CORE1.21, CORE1.533
WAVE_BUS_21: CORE1.22, CORE1.534
WAVE_BUS_22: CORE1.23, CORE1.535
WAVE_BUS_23: CORE1.24, CORE1.280, CORE1.536
WAVE_BUS_24: CORE1.25, CORE1.281, CORE1.537
WAVE_BUS_25: CORE1.26, CORE1.282, CORE1.538
WAVE_BUS_26: CORE1.27, CORE1.283, CORE1.539
WAVE_BUS_27: CORE1.28, CORE1.284, CORE1.540
WAVE_BUS_28: CORE1.29, CORE1.285, CORE1.541
WAVE_BUS_29: CORE1.30, CORE1.286, CORE1.542
WAVE_BUS_30: CORE1.31, CORE1.287, CORE1.543
WAVE_BUS_31: CORE1.32, CORE1.288, CORE1.544
WAVE_BUS_32: CORE1.33, CORE1.289, CORE1.545
WAVE_BUS_33: CORE1.34, CORE1.290, CORE1.546
WAVE_BUS_34: CORE1.35, CORE1.291, CORE1.547
WAVE_BUS_35: CORE1.36, CORE1.292, CORE1.548
WAVE_BUS_36: CORE1.37, CORE1.293, CORE1.549
WAVE_BUS_37: CORE1.38, CORE1.294, CORE1.550
WAVE_BUS_38: CORE1.39, CORE1.295, CORE1.551
WAVE_BUS_39: CORE1.40, CORE1.296, CORE1.552
WAVE_BUS_40: CORE1.41, CORE1.297, CORE1.553
WAVE_BUS_41: CORE1.42, CORE1.554
WAVE_BUS_42: CORE1.43, CORE1.555
WAVE_BUS_43: CORE1.44, CORE1.556
WAVE_BUS_44: CORE1.45, CORE1.557
WAVE_BUS_45: CORE1.46, CORE1.558
WAVE_BUS_46: CORE1.47, CORE1.559
WAVE_BUS_47: CORE1.48, CORE1.304, CORE1.560
WAVE_BUS_48: CORE1.49, CORE1.305, CORE1.561
WAVE_BUS_49: CORE1.50, CORE1.306, CORE1.562
WAVE_BUS_50: CORE1.51, CORE1.307, CORE1.563
WAVE_BUS_51: CORE1.52, CORE1.308, CORE1.564
WAVE_BUS_52: CORE1.53, CORE1.309, CORE1.565
WAVE_BUS_53: CORE1.54, CORE1.310, CORE1.566
WAVE_BUS_54: CORE1.55, CORE1.311, CORE1.567
WAVE_BUS_55: CORE1.56, CORE1.312, CORE1.568
WAVE_BUS_56: CORE1.57, CORE1.313, CORE1.569
WAVE_BUS_57: CORE1.58, CORE1.314, CORE1.570
WAVE_BUS_58: CORE1.59, CORE1.315, CORE1.571
WAVE_BUS_59: CORE1.60, CORE1.316, CORE1.572
WAVE_BUS_60: CORE1.61, CORE1.317, CORE1.573
WAVE_BUS_61: CORE1.62, CORE1.318, CORE1.574
WAVE_BUS_62: CORE1.63, CORE1.319, CORE1.575
WAVE_BUS_63: CORE1.64, CORE1.320, CORE1.576
WAVE_BUS_64: CORE1.65, CORE1.321
WAVE_BUS_71: CORE1.72, CORE1.328
WAVE_BUS_72: CORE1.73, CORE1.329
WAVE_BUS_73: CORE1.74, CORE1.330
WAVE_BUS_74: CORE1.75, CORE1.331
WAVE_BUS_75: CORE1.76, CORE1.332
WAVE_BUS_76: CORE1.77, CORE1.333
WAVE_BUS_77: CORE1.78, CORE1.334
WAVE_BUS_78: CORE1.79, CORE1.335
WAVE_BUS_79: CORE1.80, CORE1.336
WAVE_BUS_80: CORE1.81, CORE1.337
WAVE_BUS_81: CORE1.82, CORE1.338
WAVE_BUS_82: CORE1.83, CORE1.339
WAVE_BUS_83: CORE1.84, CORE1.340
WAVE_BUS_84: CORE1.85, CORE1.341
WAVE_BUS_85: CORE1.86, CORE1.342
WAVE_BUS_86: CORE1.87, CORE1.343
WAVE_BUS_87: CORE1.88, CORE1.344
WAVE_BUS_88: CORE1.89, CORE1.345
WAVE_BUS_95: CORE1.96, CORE1.352
WAVE_BUS_96: CORE1.97, CORE1.353
WAVE_BUS_97: CORE1.98, CORE1.354
WAVE_BUS_98: CORE1.99, CORE1.355
WAVE_BUS_99: CORE1.100, CORE1.356
WAVE_BUS_100: CORE1.101, CORE1.357
WAVE_BUS_101: CORE1.102, CORE1.358
WAVE_BUS_102: CORE1.103, CORE1.359
WAVE_BUS_103: CORE1.104, CORE1.360
WAVE_BUS_104: CORE1.105, CORE1.361
WAVE_BUS_105: CORE1.106, CORE1.362
WAVE_BUS_106: CORE1.107, CORE1.363
WAVE_BUS_107: CORE1.108, CORE1.364
WAVE_BUS_108: CORE1.109, CORE1.365
WAVE_BUS_109: CORE1.110, CORE1.366
WAVE_BUS_110: CORE1.111, CORE1.367
WAVE_BUS_111: CORE1.112, CORE1.368
WAVE_BUS_112: CORE1.113, CORE1.369
WAVE_BUS_113: CORE1.114, CORE1.370
WAVE_BUS_114: CORE1.115, CORE1.371
WAVE_BUS_115: CORE1.116, CORE1.372
WAVE_BUS_116: CORE1.117, CORE1.373
WAVE_BUS_117: CORE1.118, CORE1.374
WAVE_BUS_118: CORE1.119, CORE1.375
WAVE_BUS_119: CORE1.120, CORE1.376
WAVE_BUS_120: CORE1.121, CORE1.377
WAVE_BUS_121: CORE1.122, CORE1.378
WAVE_BUS_122: CORE1.123, CORE1.379
WAVE_BUS_123: CORE1.124, CORE1.380
WAVE_BUS_124: CORE1.125, CORE1.381
WAVE_BUS_125: CORE1.126, CORE1.382
WAVE_BUS_126: CORE1.127, CORE1.383
WAVE_BUS_127: CORE1.128, CORE1.384
WAVE_BUS_128: CORE1.129, CORE1.385
WAVE_BUS_129: CORE1.130, CORE1.386
WAVE_BUS_130: CORE1.131, CORE1.387
WAVE_BUS_131: CORE1.132, CORE1.388
WAVE_BUS_132: CORE1.133, CORE1.389
WAVE_BUS_133: CORE1.134, CORE1.390
WAVE_BUS_134: CORE1.135, CORE1.391
WAVE_BUS_135: CORE1.136, CORE1.392
WAVE_BUS_136: CORE1.137, CORE1.393
WAVE_BUS_137: CORE1.138, CORE1.394
WAVE_BUS_138: CORE1.139, CORE1.395
WAVE_BUS_139: CORE1.140, CORE1.396
WAVE_BUS_140: CORE1.141, CORE1.397
WAVE_BUS_141: CORE1.142, CORE1.398
WAVE_BUS_142: CORE1.143, CORE1.399
WAVE_BUS_143: CORE1.144, CORE1.400
WAVE_BUS_144: CORE1.145, CORE1.401
WAVE_BUS_145: CORE1.146, CORE1.402
WAVE_BUS_146: CORE1.147, CORE1.403
WAVE_BUS_147: CORE1.148, CORE1.404
WAVE_BUS_148: CORE1.149, CORE1.405
WAVE_BUS_149: CORE1.150, CORE1.406
WAVE_BUS_150: CORE1.151, CORE1.407
WAVE_BUS_151: CORE1.152, CORE1.408
WAVE_BUS_152: CORE1.153, CORE1.409
WAVE_BUS_153: CORE1.154, CORE1.410
WAVE_BUS_154: CORE1.155, CORE1.411
WAVE_BUS_155: CORE1.156, CORE1.412
WAVE_BUS_156: CORE1.157, CORE1.413
WAVE_BUS_157: CORE1.158, CORE1.414
WAVE_BUS_158: CORE1.159, CORE1.415
WAVE_BUS_159: CORE1.160, CORE1.416
WAVE_BUS_160: CORE1.161, CORE1.417
WAVE_BUS_161: CORE1.162, CORE1.418
WAVE_BUS_162: CORE1.163, CORE1.419
WAVE_BUS_163: CORE1.164, CORE1.420
WAVE_BUS_164: CORE1.165, CORE1.421
WAVE_BUS_165: CORE1.166, CORE1.422
WAVE_BUS_166: CORE1.167, CORE1.423
WAVE_BUS_167: CORE1.168, CORE1.424
WAVE_BUS_168: CORE1.169, CORE1.425
WAVE_BUS_169: CORE1.170, CORE1.426
WAVE_BUS_170: CORE1.171, CORE1.427
WAVE_BUS_171: CORE1.172, CORE1.428
WAVE_BUS_172: CORE1.173, CORE1.429
WAVE_BUS_173: CORE1.174, CORE1.430
WAVE_BUS_174: CORE1.175, CORE1.431
WAVE_BUS_175: CORE1.176, CORE1.432
WAVE_BUS_176: CORE1.177, CORE1.433
WAVE_BUS_177: CORE1.178, CORE1.434
WAVE_BUS_178: CORE1.179, CORE1.435
WAVE_BUS_179: CORE1.180, CORE1.436
WAVE_BUS_180: CORE1.181, CORE1.437
WAVE_BUS_181: CORE1.182, CORE1.438
WAVE_BUS_182: CORE1.183, CORE1.439
WAVE_BUS_183: CORE1.184, CORE1.440
WAVE_BUS_184: CORE1.185, CORE1.441
WAVE_BUS_185: CORE1.186, CORE1.442
WAVE_BUS_186: CORE1.187, CORE1.443
WAVE_BUS_187: CORE1.188, CORE1.444
WAVE_BUS_188: CORE1.189, CORE1.445
WAVE_BUS_189: CORE1.190, CORE1.446
WAVE_BUS_190: CORE1.191, CORE1.447
WAVE_BUS_191: CORE1.192, CORE1.448
WAVE_BUS_192: CORE1.193, CORE1.449
WAVE_BUS_193: CORE1.194, CORE1.450
WAVE_BUS_194: CORE1.195, CORE1.451
WAVE_BUS_195: CORE1.196, CORE1.452
WAVE_BUS_196: CORE1.197, CORE1.453
WAVE_BUS_197: CORE1.198, CORE1.454
WAVE_BUS_198: CORE1.199, CORE1.455
WAVE_BUS_199: CORE1.200, CORE1.456
WAVE_BUS_200: CORE1.201, CORE1.457
WAVE_BUS_201: CORE1.202, CORE1.458
WAVE_BUS_202: CORE1.203, CORE1.459
WAVE_BUS_203: CORE1.204, CORE1.460
WAVE_BUS_204: CORE1.205, CORE1.461
WAVE_BUS_205: CORE1.206, CORE1.462
WAVE_BUS_206: CORE1.207, CORE1.463
WAVE_BUS_207: CORE1.208, CORE1.464
WAVE_BUS_208: CORE1.209, CORE1.465
WAVE_BUS_209: CORE1.210, CORE1.466
WAVE_BUS_210: CORE1.211, CORE1.467
WAVE_BUS_211: CORE1.212, CORE1.468
WAVE_BUS_212: CORE1.213, CORE1.469
WAVE_BUS_213: CORE1.214, CORE1.470
WAVE_BUS_214: CORE1.215, CORE1.471
WAVE_BUS_215: CORE1.216, CORE1.472
WAVE_BUS_216: CORE1.217, CORE1.473
WAVE_BUS_217: CORE1.218, CORE1.474
WAVE_BUS_218: CORE1.219, CORE1.475
WAVE_BUS_219: CORE1.220, CORE1.476
WAVE_BUS_220: CORE1.221, CORE1.477
WAVE_BUS_221: CORE1.222, CORE1.478
WAVE_BUS_222: CORE1.223, CORE1.479
WAVE_BUS_223: CORE1.224, CORE1.480
WAVE_BUS_224: CORE1.225, CORE1.481
WAVE_BUS_231: CORE1.232, CORE1.488
WAVE_BUS_232: CORE1.233, CORE1.489
WAVE_BUS_233: CORE1.234, CORE1.490
WAVE_BUS_234: CORE1.235, CORE1.491
WAVE_BUS_235: CORE1.236, CORE1.492
WAVE_BUS_236: CORE1.237, CORE1.493
WAVE_BUS_237: CORE1.238, CORE1.494
WAVE_BUS_238: CORE1.239, CORE1.495
WAVE_BUS_239: CORE1.240, CORE1.496
WAVE_BUS_240: CORE1.241, CORE1.497
WAVE_BUS_241: CORE1.242, CORE1.498
WAVE_BUS_242: CORE1.243, CORE1.499
WAVE_BUS_243: CORE1.244, CORE1.500
WAVE_BUS_244: CORE1.245, CORE1.501
WAVE_BUS_245: CORE1.246, CORE1.502
WAVE_BUS_246: CORE1.247, CORE1.503
WAVE_BUS_247: CORE1.248, CORE1.504
WAVE_BUS_248: CORE1.249, CORE1.505
WAVE_BUS_255: CORE1.256, CORE1.512
